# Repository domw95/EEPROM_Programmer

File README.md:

# EEPROM Programmer board based on Arduino Mega
For flashing AT28Cx style 28 pin parallel EEPROM ICs

## Hardware
- Standard 28 pin socket or lever quick release socket
- Indicator LEDs for address, data and control pins
- Connectors for programming external devices

## Firmware
- Library functions for reading and writing to EEPROM
- Example for flashing logic for 4 digit 7-segment display

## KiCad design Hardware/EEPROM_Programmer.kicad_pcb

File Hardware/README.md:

# Hardware
## Issues/Improvements
- Decoupling capacitor should be closer to EEPROM
- Reset button for arduino would be useful
- General purpose button
- Header for 5V

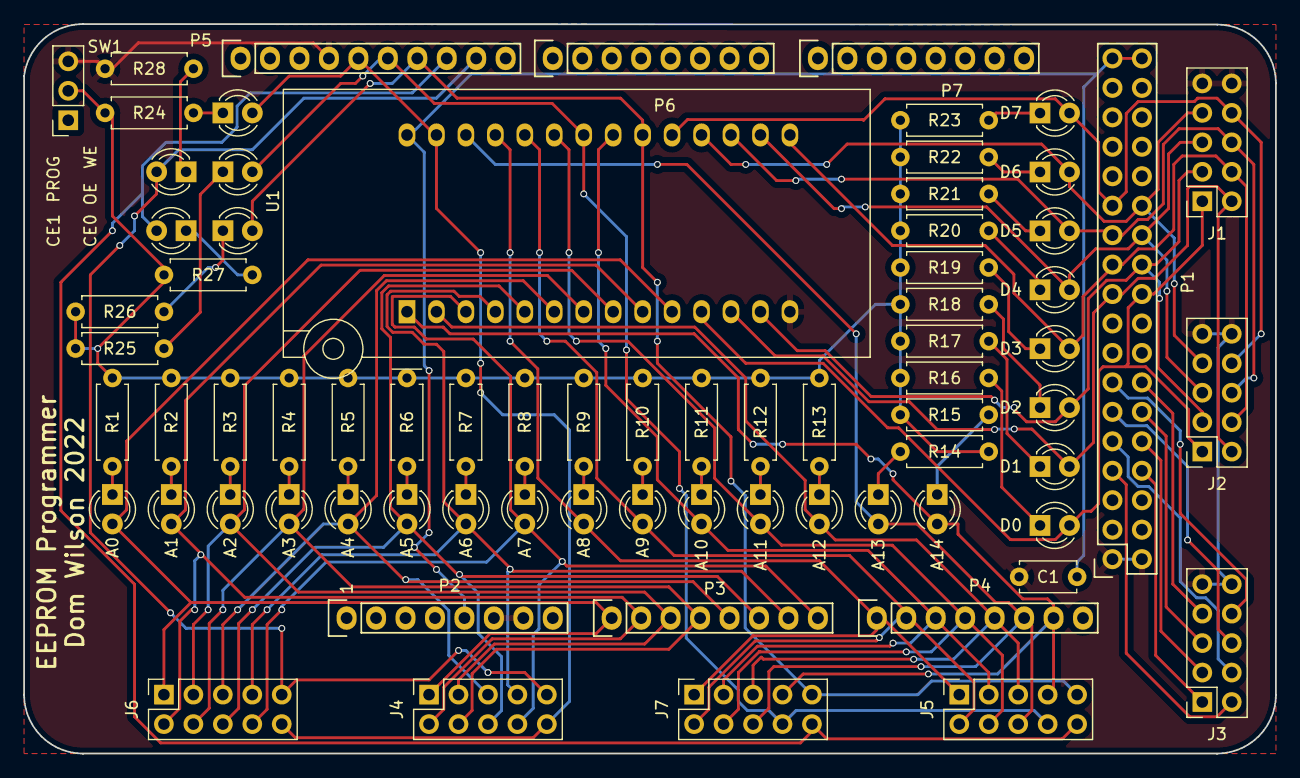
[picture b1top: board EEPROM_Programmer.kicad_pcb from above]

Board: 2 copper layers, 108.0 x 62.9 mm, 73 parts (0 on the bottom side), 67 nets.

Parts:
A0, A1, A2, A3, A4, A5, A6, A7, A8, A9, A10, A11, A12, A13, A14: LED; LED_D3.0mm
C1: C; C_Disc_D4.7mm_W2.5mm_P5.00mm
CE0, CE1: LED; LED_D3.0mm
D0, D1, D2, D3, D4, D5, D6, D7: LED; LED_D3.0mm
J1, J2, J3, J4, J5, J6, J7: Conn_02x05_Odd_Even; PinSocket_2x05_P2.54mm_Vertical
OE: LED; LED_D3.0mm
P1: Digital; Socket_Strip_Arduino_2x18
P2: Power; Socket_Strip_Arduino_1x08
P3, P4: Analog; Socket_Strip_Arduino_1x08
P5: PWM; Socket_Strip_Arduino_1x10
P6: PWM; Socket_Strip_Arduino_1x08
P7: Communication; Socket_Strip_Arduino_1x08
PROG: LED; LED_D3.0mm
R1, R2, R3, R4, R5, R6, R7, R8, R9, R10, R11, R12, R13, R14, R15, R16, R17, R18, R19, R20, R21, R22, R23, R24, R25, R26, R27, R28: R; R_Axial_DIN0207_L6.3mm_D2.5mm_P7.62mm_Horizontal
SW1: SW_SPDT; PinSocket_1x03_P2.54mm_Vertical
U1: 28C256; DIP_Socket-28_W11.9_W12.7_W15.24_W17.78_W18.5_3M_228-1277-0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
WE: LED; LED_D3.0mm

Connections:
+5V: C1.1, P1.35, P1.36, P2.5, U1.28 (VCC)
/9(**): J4.9, J6.9, P5.9, PROG.2 (A)
/10(**): CE1.2 (A), J5.10, J7.10, P5.8
/11(**): CE0.2 (A), J5.9, J7.9, P5.7, U1.20 (~CS)
/12(**): J5.8, J7.8, OE.2 (A), P5.6, U1.22 (~OE)
/13(**): J4.10, J6.10, P5.5, U1.27 (~WE), WE.2 (A)
/30: D7.2 (A), J1.8, J2.8, P1.25, U1.19 (D7)
/31: D6.2 (A), J1.7, J2.7, P1.26, U1.18 (D6)
/32: D5.2 (A), J1.6, J2.6, P1.23, U1.17 (D5)
/33: D4.2 (A), J1.5, J2.5, P1.24, U1.16 (D4)
/34: D3.2 (A), J1.4, J2.4, P1.21, U1.15 (D3)
/35: D2.2 (A), J1.3, J2.3, P1.22, U1.13 (D2)
/36: D1.2 (A), J1.2, J2.2, P1.19, U1.12 (D1)
/37: D0.2 (A), J1.1, J2.1, P1.20, U1.11 (D0)
/42: J3.8, P1.13
/43: J3.7, P1.14
/44: J3.6, P1.11
/45: J3.5, P1.12
/46: J3.4, P1.9
/47: J3.3, P1.10
/48: J3.2, P1.7
/49: J3.1, P1.8
/A0: A0.2 (A), J4.1, J6.1, P3.1, U1.10 (A0)
/A1: A1.2 (A), J4.2, J6.2, P3.2, U1.9 (A1)
/A2: A2.2 (A), J4.3, J6.3, P3.3, U1.8 (A2)
/A3: A3.2 (A), J4.4, J6.4, P3.4, U1.7 (A3)
/A4: A4.2 (A), J4.5, J6.5, P3.5, U1.6 (A4)
/A5: A5.2 (A), J4.6, J6.6, P3.6, U1.5 (A5)
/A6: A6.2 (A), J4.7, J6.7, P3.7, U1.4 (A6)
/A7: A7.2 (A), J4.8, J6.8, P3.8, U1.3 (A7)
/A8: A8.2 (A), J5.1, J7.1, P4.1, U1.25 (A8)
/A9: A9.2 (A), J5.2, J7.2, P4.2, U1.24 (A9)
/A10: A10.2 (A), J5.3, J7.3, P4.3, U1.21 (A10)
/A11: A11.2 (A), J5.4, J7.4, P4.4, U1.23 (A11)
/A12: A12.2 (A), J5.5, J7.5, P4.5, U1.2 (A12)
/A13: A13.2 (A), J5.6, J7.6, P4.6, U1.26 (A13)
/A14: A14.2 (A), J5.7, J7.7, P4.7, U1.1 (A14)
GND: C1.2, J1.9, J1.10, J2.9, J2.10, J3.9, J3.10, P1.1, P1.2, P2.6, P2.7, P5.4, R28.1, SW1.3 (C), U1.14 (GND)
unnamed: A0.1 (K), R1.2
unnamed: A1.1 (K), R2.2
unnamed: A2.1 (K), R3.2
unnamed: A3.1 (K), R4.2
unnamed: A4.1 (K), R5.2
unnamed: A5.1 (K), R6.2
unnamed: A6.1 (K), R7.2
unnamed: A7.1 (K), R8.2
unnamed: A8.1 (K), R9.2
unnamed: A9.1 (K), R10.2
unnamed: A10.1 (K), R11.2
unnamed: A11.1 (K), R12.2
unnamed: A12.1 (K), R13.2
unnamed: A13.1 (K), R14.2
unnamed: A14.1 (K), R15.2
unnamed: CE0.1 (K), R26.2
unnamed: CE1.1 (K), R27.2
unnamed: D0.1 (K), R16.2
unnamed: D1.1 (K), R17.2
unnamed: D2.1 (K), R18.2
unnamed: D3.1 (K), R19.2
unnamed: D4.1 (K), R20.2
unnamed: D5.1 (K), R21.2
unnamed: D6.1 (K), R22.2
unnamed: D7.1 (K), R23.2
unnamed: OE.1 (K), R25.2
unnamed: PROG.1 (K), R28.2
unnamed: R1.1, R2.1, R3.1, R4.1, R5.1, R6.1, R7.1, R8.1, R9.1, R10.1, R11.1, R12.1, R13.1, R14.1, R15.1, R16.1, R17.1, R18.1, R19.1, R20.1, R21.1, R22.1, R23.1, R24.1, R25.1, R26.1, R27.1, SW1.2 (B)
unnamed: R24.2, WE.1 (K)

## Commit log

2022-08-13 Flash Display EEPROM Functional
2022-08-13 Added Kicad project
2022-08-13 Added README
2022-08-13 Updated READMEs
2022-08-13 Added hardware README
2022-08-14 Updated delay time
2022-08-14 Added more issues
2022-08-14 Added write and verify function
2022-08-14 Started bit shifter logic
2022-08-30 Readme
2022-08-30 Memory checker for IC testing
2022-08-30 Library for testing modules and assemblies
2022-08-30 Firmware for testing register module
2022-08-30 Firmware for testing adder module
2022-08-30 Firmware for testing display module
2023-03-04 ignore binaries
2023-03-04 Programs to test module functionality
